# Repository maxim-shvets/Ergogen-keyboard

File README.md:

<h1>THIS README IS A WORK IN PROGRESS</h1>
<h1>"Keyboard Name" v1</h1>
Name is a wireless, # key split column-splayed and column-staggered ergonomic choc switch keyboard with a large thumb cluster. Each half uses a Nice!Nano v2 and supports an OLED display.
<h2>Photo</h2>
(insert photo)
<h2>Parts list</h2>

- 2 x PCB (Gerber file located here)
- 2 x Nice!Nano v2 ([I used this AliExpress knockoff](https://www.aliexpress.us/item/3256807079797756.html?spm=a2g0o.cart.0.0.729138daYP96Yi&mp=1&pdp_npi=6%40dis%21USD%21USD+24.09%21USD+22.09%21%21USD+22.09%21%21%21%402101c44f17780205030602267ea1ad%2112000055967601728%21ct%21US%21-1%21%211%210%21&_gl=1*yoof1g*_gcl_aw*R0NMLjE3NzgwMDIxNDEuQ2p3S0NBandxdWJQQmhCT0Vpd0F6Z1pYMmtac0k4MDQ5NmhrZnZ1X3EyQU5pSkd6XzZWeS1HSXVTbFpKMjRHNHN0VTRLengwdU05WXdob0NLZThRQXZEX0J3RQ..*_gcl_dc*R0NMLjE3NzgwMDIxNDEuQ2p3S0NBandxdWJQQmhCT0Vpd0F6Z1pYMmtac0k4MDQ5NmhrZnZ1X3EyQU5pSkd6XzZWeS1HSXVTbFpKMjRHNHN0VTRLengwdU05WXdob0NLZThRQXZEX0J3RQ..*_gcl_au*OTYzNjA3OC4xNzc4MDAxNDI4*_ga*MTM1NDcyNzk2Mi4xNzc4MDAxNDQ0*_ga_VED1YSGNC7*czE3NzgwMjA0ODgkbzMkZzEkdDE3NzgwMjA4ODgkajYwJGwwJGgw&gatewayAdapt=glo2usa))
- 2 x Pair of female headers for the N!N ([Here](https://www.amazon.com/Ferwooh-Single-Straight-Connector-Spacing/dp/B0CZ6X313F/ref=sr_1_3?crid=23UBIGV2P5FY2&dib=eyJ2IjoiMSJ9.my1z_XJlQFrNgZNH_tsevyGhxeroAV_GrkD1v3mq-l9fa3hd-9JNAOj0Gcp6buJBHgkzMY5yk75Po8QivGPEscL_T5TmnE404585GF-qNXK7jS7XaAhcegh0n_mB7tFkkd3OV8gE6qr_BxLupvwGOJPKAuQelEq9BL9b04RVhLT3cPO27XIjlwhg4oeBcS6HaBLxP6c8edkcudrdGfZsJB2oC93_Rdd2d6SHhLjnteU.fBmBkXcev_xrGZxBnmeQ5HpRHx399pl9aDxiEuDQfPs&dib_tag=se&keywords=female+header+pins&qid=1778023583&sprefix=%2Caps%2C162&sr=8-3))
- 2 x Battery ([Here](https://www.amazon.com/Replacement-Playstation-Controller-CECHZC2E-CECHZC2U-3/dp/B09726K2LC))
- 2 x Battery connector ([Here](https://www.aliexpress.us/item/3256808513587950.html?spm=a2g0o.productlist.main.15.4e79ioQxioQxse&algo_pvid=0916d4c9-59a7-43de-b7df-8fc46e0a34de&algo_exp_id=0916d4c9-59a7-43de-b7df-8fc46e0a34de-14&pdp_ext_f=%7B%22order%22%3A%2264%22%2C%22eval%22%3A%221%22%2C%22fromPage%22%3A%22search%22%7D&pdp_npi=6%40dis%21USD%211.93%211.89%21%21%211.93%211.89%21%402101ea8c17780208337528485e14b7%2112000046305318073%21sea%21US%210%21ABX%211%210%21n_tag%3A-29910%3Bd%3A59837f2c%3Bm03_new_user%3A-29895&curPageLogUid=ugDkaPqFfBxg&utparam-url=scene%3Asearch%7Cquery_from%3A%7Cx_object_id%3A1005008699902702%7C_p_origin_prod%3A))
- 2 x Power switch ([Here](https://www.aliexpress.us/item/3256808633680624.html?spm=a2g0o.cart.0.0.729138daYP96Yi&mp=1&pdp_npi=6%40dis%21USD%21USD+3.24%21USD+1.24%21%21USD+1.24%21%21%21%402101c44f17780205030602267ea1ad%2112000046807131577%21ct%21US%21-1%21%211%210%21&_gl=1*wnxu58*_gcl_aw*R0NMLjE3NzgwMDIxNDEuQ2p3S0NBandxdWJQQmhCT0Vpd0F6Z1pYMmtac0k4MDQ5NmhrZnZ1X3EyQU5pSkd6XzZWeS1HSXVTbFpKMjRHNHN0VTRLengwdU05WXdob0NLZThRQXZEX0J3RQ..*_gcl_dc*R0NMLjE3NzgwMDIxNDEuQ2p3S0NBandxdWJQQmhCT0Vpd0F6Z1pYMmtac0k4MDQ5NmhrZnZ1X3EyQU5pSkd6XzZWeS1HSXVTbFpKMjRHNHN0VTRLengwdU05WXdob0NLZThRQXZEX0J3RQ..*_gcl_au*OTYzNjA3OC4xNzc4MDAxNDI4*_ga*MTM1NDcyNzk2Mi4xNzc4MDAxNDQ0*_ga_VED1YSGNC7*czE3NzgwMjA0ODgkbzMkZzEkdDE3NzgwMjA5ODYkajU3JGwwJGgw&gatewayAdapt=glo2usa))
- 2 x Reset/flash button ([Here](https://www.aliexpress.us/item/3256812007763842.html?spm=a2g0o.cart.0.0.47d738dahjfSD9&mp=1&pdp_npi=6%40dis%21USD%21USD+1.50%21USD+0.99%21%21USD+0.99%21%21%21%40210319b717780228258443855ee8e3%2112000057719893273%21ct%21US%212774339235%21%211%210%21&pdp_ext_f=%7B%22cart2PdpParams%22%3A%7B%22pdpBusinessMode%22%3A%22retail%22%7D%7D&_gl=1*17stnxq*_gcl_aw*R0NMLjE3NzgwMDIxNDEuQ2p3S0NBandxdWJQQmhCT0Vpd0F6Z1pYMmtac0k4MDQ5NmhrZnZ1X3EyQU5pSkd6XzZWeS1HSXVTbFpKMjRHNHN0VTRLengwdU05WXdob0NLZThRQXZEX0J3RQ..*_gcl_dc*R0NMLjE3NzgwMDIxNDEuQ2p3S0NBandxdWJQQmhCT0Vpd0F6Z1pYMmtac0k4MDQ5NmhrZnZ1X3EyQU5pSkd6XzZWeS1HSXVTbFpKMjRHNHN0VTRLengwdU05WXdob0NLZThRQXZEX0J3RQ..*_gcl_au*OTYzNjA3OC4xNzc4MDAxNDI4*_ga*MTM1NDcyNzk2Mi4xNzc4MDAxNDQ0*_ga_VED1YSGNC7*czE3NzgwMjA0ODgkbzMkZzEkdDE3NzgwMjM1MjYkajUyJGwwJGgw&gatewayAdapt=glo2usa))
- number x Keycaps X (Here)
- 2 x Keycaps Y (Here)
- number x Kailh Choc Hot Swap Sockets ([Here](https://www.aliexpress.us/item/3256808918805272.html?spm=a2g0o.cart.0.0.47d738dahjfSD9&mp=1&pdp_npi=6%40dis%21USD%21USD+19.50%21USD+11.70%21%21USD+11.70%21%21%21%40210319b717780228258443855ee8e3%2112000047980288822%21ct%21US%212774339235%21%211%210%21&_gl=1*1e1f932*_gcl_aw*R0NMLjE3NzgwMDIxNDEuQ2p3S0NBandxdWJQQmhCT0Vpd0F6Z1pYMmtac0k4MDQ5NmhrZnZ1X3EyQU5pSkd6XzZWeS1HSXVTbFpKMjRHNHN0VTRLengwdU05WXdob0NLZThRQXZEX0J3RQ..*_gcl_dc*R0NMLjE3NzgwMDIxNDEuQ2p3S0NBandxdWJQQmhCT0Vpd0F6Z1pYMmtac0k4MDQ5NmhrZnZ1X3EyQU5pSkd6XzZWeS1HSXVTbFpKMjRHNHN0VTRLengwdU05WXdob0NLZThRQXZEX0J3RQ..*_gcl_au*OTYzNjA3OC4xNzc4MDAxNDI4*_ga*MTM1NDcyNzk2Mi4xNzc4MDAxNDQ0*_ga_VED1YSGNC7*czE3NzgwMjA0ODgkbzMkZzEkdDE3NzgwMjM2NTgkajI4JGwwJGgw&gatewayAdapt=glo2usa))
- number x Kailh Choch switches of your choice
- number x SMD diodes (SOD-123 MAKE SURE THIS IS CORRECT) ([Here](https://www.aliexpress.us/item/3256810466885186.html?spm=a2g0o.cart.0.0.729138daYP96Yi&mp=1&pdp_npi=6%40dis%21USD%21USD+3.85%21USD+0.99%21%21USD+0.99%21%21%21%402101c44f17780205030602267ea1ad%2112000053087454998%21ct%21US%21-1%21%211%210%21&_gl=1*12gcs97*_gcl_aw*R0NMLjE3NzgwMDIxNDEuQ2p3S0NBandxdWJQQmhCT0Vpd0F6Z1pYMmtac0k4MDQ5NmhrZnZ1X3EyQU5pSkd6XzZWeS1HSXVTbFpKMjRHNHN0VTRLengwdU05WXdob0NLZThRQXZEX0J3RQ..*_gcl_dc*R0NMLjE3NzgwMDIxNDEuQ2p3S0NBandxdWJQQmhCT0Vpd0F6Z1pYMmtac0k4MDQ5NmhrZnZ1X3EyQU5pSkd6XzZWeS1HSXVTbFpKMjRHNHN0VTRLengwdU05WXdob0NLZThRQXZEX0J3RQ..*_gcl_au*OTYzNjA3OC4xNzc4MDAxNDI4*_ga*MTM1NDcyNzk2Mi4xNzc4MDAxNDQ0*_ga_VED1YSGNC7*czE3NzgwMjA0ODgkbzMkZzEkdDE3NzgwMjEwMzkkajQkbDAkaDA.&gatewayAdapt=glo2usa))
- (Optional) 2 x OLED display* ([Here](https://www.aliexpress.us/item/3256810111446013.html?spm=a2g0o.cart.0.0.729138daYP96Yi&mp=1&pdp_npi=6%40dis%21USD%21USD+16.11%21USD+0.99%21%21USD+0.99%21%21%21%402101c44f17780205030602267ea1ad%2112000051836100906%21ct%21US%21-1%21%211%210%21&_gl=1*phfqy9*_gcl_aw*R0NMLjE3NzgwMDIxNDEuQ2p3S0NBandxdWJQQmhCT0Vpd0F6Z1pYMmtac0k4MDQ5NmhrZnZ1X3EyQU5pSkd6XzZWeS1HSXVTbFpKMjRHNHN0VTRLengwdU05WXdob0NLZThRQXZEX0J3RQ..*_gcl_dc*R0NMLjE3NzgwMDIxNDEuQ2p3S0NBandxdWJQQmhCT0Vpd0F6Z1pYMmtac0k4MDQ5NmhrZnZ1X3EyQU5pSkd6XzZWeS1HSXVTbFpKMjRHNHN0VTRLengwdU05WXdob0NLZThRQXZEX0J3RQ..*_gcl_au*OTYzNjA3OC4xNzc4MDAxNDI4*_ga*MTM1NDcyNzk2Mi4xNzc4MDAxNDQ0*_ga_VED1YSGNC7*czE3NzgwMjA0ODgkbzMkZzEkdDE3NzgwMjExMTUkajEyJGwwJGgw&gatewayAdapt=glo2usa))
<h6>*It's a good idea to buy extra parts just in case</h6>
<h6>*OLEDs drain battery extremley quickly but is extremley awesome</h6>

<h2>Assembly process</h2>
(insert process)
<h2>Credits</h2>
(insert credits)
<h2>Licensing</h2>
(insert Licensing)

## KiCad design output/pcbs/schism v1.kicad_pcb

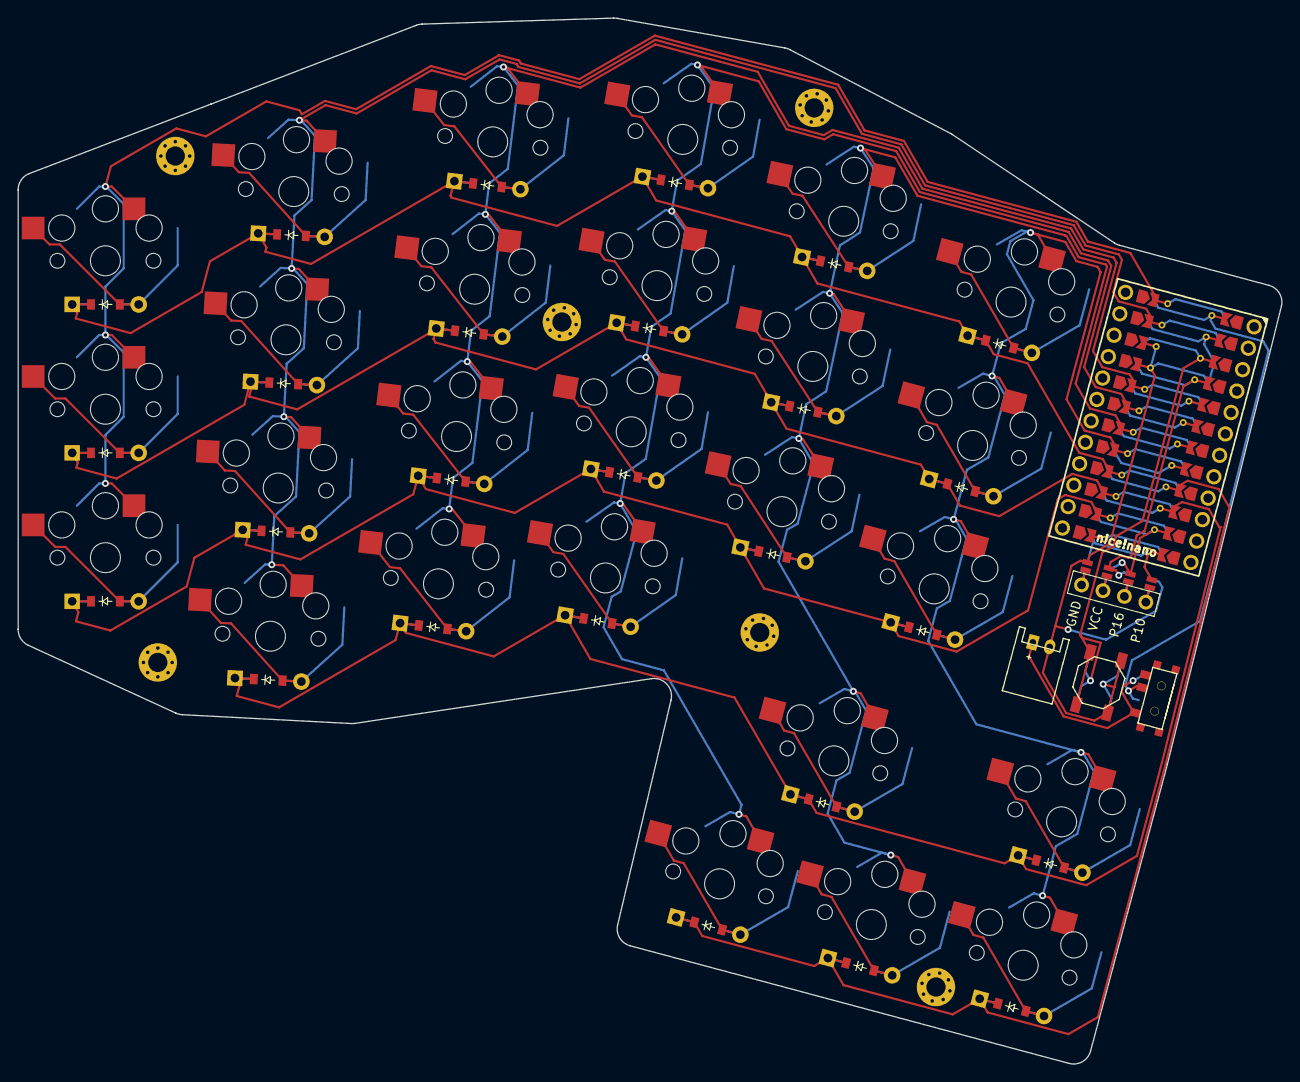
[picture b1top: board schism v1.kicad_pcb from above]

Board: 2 copper layers, 144.7 x 119.8 mm, 63 parts (0 on the bottom side), 48 nets.

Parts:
B1: SW_TACT_ALPS_SKQGABE010
D1, D2, D3, D4, D5, D6, D7, D8, D9, D10, D11, D12, D13, D14, D15, D16, D17, D18, D19, D20, D21, D22, D23, D24, D25, D26: ComboDiode
DISP1: display_ssd1306
JST1: JST_PH_S2B-PH-K_02x2.00mm_Angled
MCU1: nice!nano_v2
S1, S2, S3, S4, S5, S6, S7, S8, S9, S10, S11, S12, S13, S14, S15, S16, S17, S18, S19, S20, S21, S22, S23, S24, S25, S26: PG1350
T1: SPDT_C128955
_1, _2, _3, _4, _5, _6: MountingHole_2.2mm_M2_Pad_Via

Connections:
DISP1_1: DISP1.1, DISP1.10, DISP1.23
DISP1_2: DISP1.2, DISP1.11, DISP1.22
DISP1_3: DISP1.3, DISP1.12, DISP1.21
DISP1_4: DISP1.4, DISP1.13, DISP1.20
GND: B1.1, DISP1.14, DISP1.24, JST1.2, MCU1.GND
P0: MCU1.P0, S4.1, S5.1, S6.1, S7.1
P1: MCU1.P1, S1.1, S2.1, S3.1
P2: MCU1.P2, S8.1, S9.1, S10.1, S11.1
P3: MCU1.P3, S12.1, S13.1, S14.1, S15.1, S24.1
P4: MCU1.P4, S16.1, S17.1, S18.1, S22.1, S25.1
P5: MCU1.P5, S19.1, S20.1, S21.1, S23.1, S26.1
P6: D3.1, D7.1, D11.1, D15.1, D18.1, D21.1, MCU1.P6
P7: D2.1, D6.1, D10.1, D14.1, D17.1, D20.1, MCU1.P7
P8: D1.1, D5.1, D9.1, D13.1, D16.1, D19.1, MCU1.P8
P10: DISP1.17, DISP1.27, MCU1.P10
P14: D4.1, D8.1, D12.1, D22.1, D23.1, MCU1.P14
P15: D24.1, D25.1, D26.1, MCU1.P15
P16: DISP1.16, DISP1.26, MCU1.P16
RAW: MCU1.B+, T1.2
RST: B1.2, MCU1.RST
VCC: DISP1.15, DISP1.25, MCU1.VCC
index_bottom: D16.2, S16.2
index_home: D17.2, S17.2
index_top: D18.2, S18.2
inner_bottom: D19.2, S19.2
inner_home: D20.2, S20.2
inner_top: D21.2, S21.2
left_main: D24.2, S24.2
left_top: D22.2, S22.2
mid_main: D25.2, S25.2
mid_top: D23.2, S23.2
middle_bottom: D13.2, S13.2
middle_home: D14.2, S14.2
middle_mods: D12.2, S12.2
middle_top: D15.2, S15.2
pinky_bottom: D5.2, S5.2
pinky_home: D6.2, S6.2
pinky_mods: D4.2, S4.2
pinky_top: D7.2, S7.2
pos: JST1.1, T1.1
right_main: D26.2, S26.2
ring_bottom: D9.2, S9.2
ring_home: D10.2, S10.2
ring_mods: D8.2, S8.2
ring_top: D11.2, S11.2
tabs_bottom: D1.2, S1.2
tabs_home: D2.2, S2.2
tabs_top: D3.2, S3.2

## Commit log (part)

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2026-04-23 added the project files
2026-04-23 Create README.md for keyboard project
    Added initial content for keyboard project documentation.
2026-04-23 Update README to indicate work in progress
    Add a note indicating that the README is a work in progress.
2026-04-24 Added quick link to readme
2026-05-03 Fix rotation value in config.yaml (minor bug)
2026-05-05 Enhance parts list with links and formatting
    Updated parts list with links and improved formatting.
2026-05-05 Added a couple links
2026-05-06 Final version for pcb routing, also changed name to schism v1 (cases will come later)
2026-05-06 routed full pcb
2026-05-07 final routed pcb and gerber test files for manufacturing (will add name and art to pcb soon
